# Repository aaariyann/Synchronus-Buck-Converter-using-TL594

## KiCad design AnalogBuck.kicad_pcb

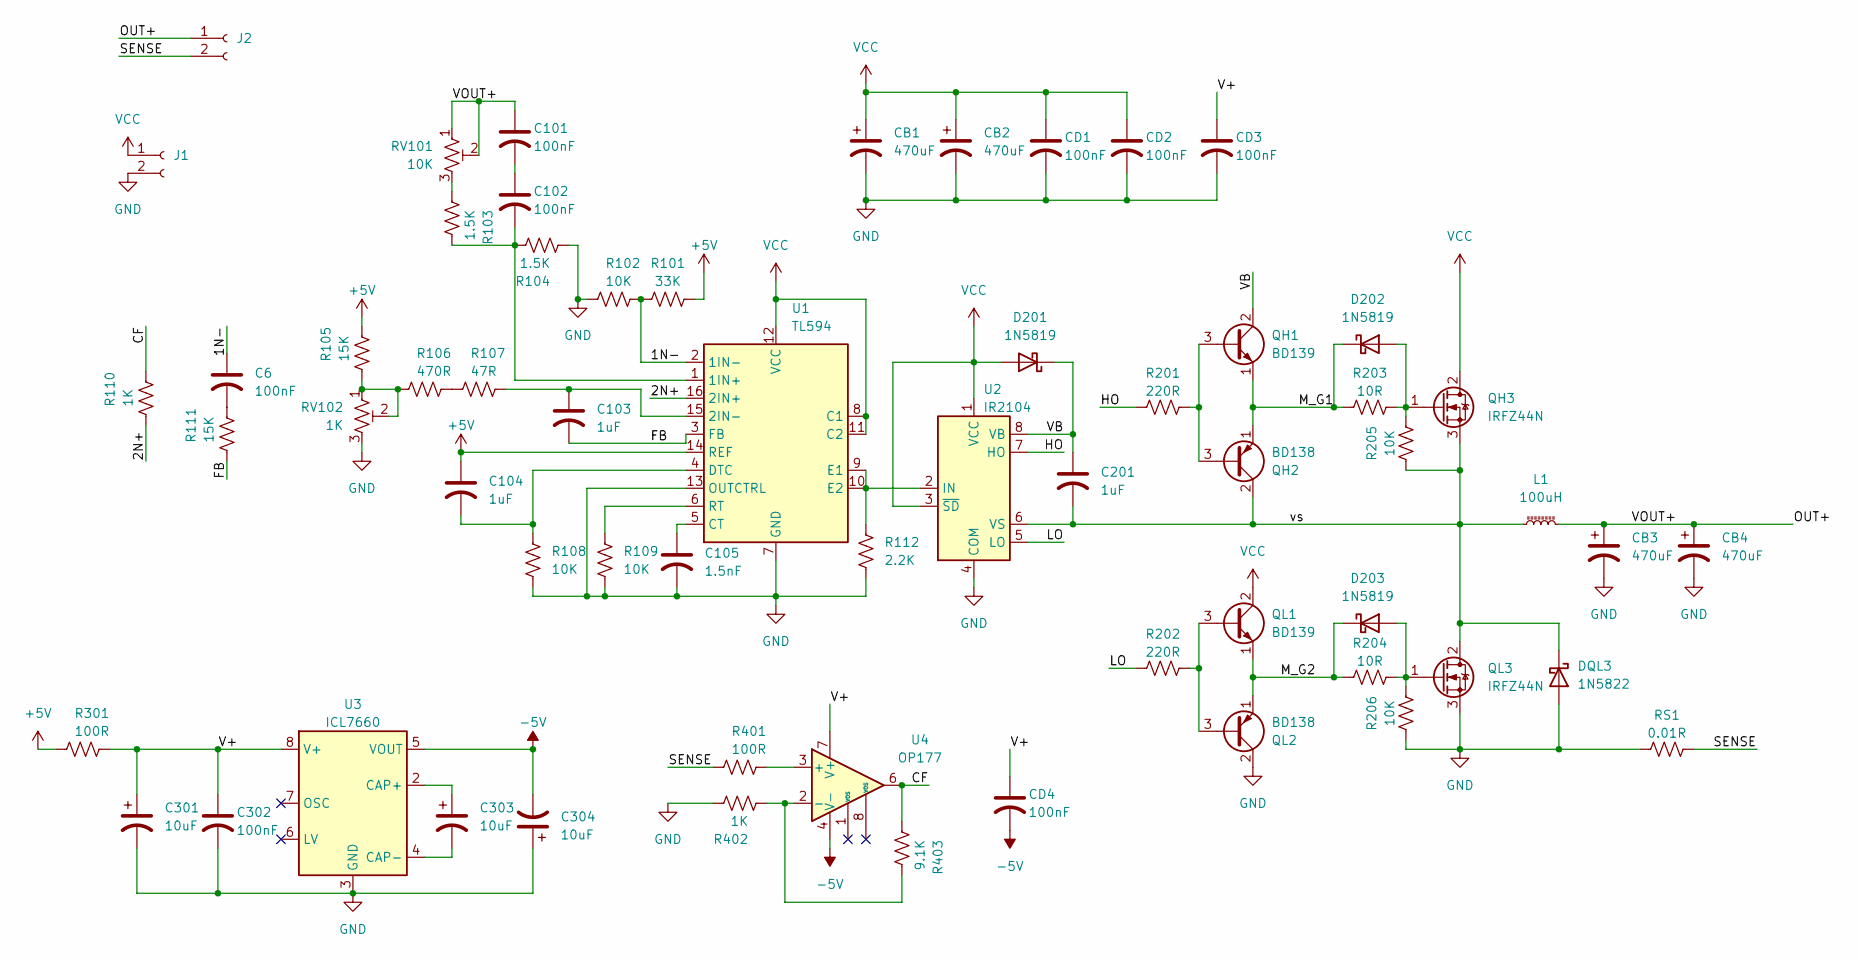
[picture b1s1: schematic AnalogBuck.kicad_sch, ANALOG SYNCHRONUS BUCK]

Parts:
C6, C101, C102, C302: 100nF; C_Disc_D5.0mm_W2.5mm_P5.00mm
C103, C104, C201: 1uF; C_Rect_L16.5mm_W4.7mm_P15.00mm_MKT
C105: 1.5nF; C_Rect_L7.0mm_W2.0mm_P5.00mm
C301, C303, C304: 10uF; CP_Radial_D5.0mm_P2.50mm
CB1, CB2, CB3, CB4: 470uF; CP_Radial_D8.0mm_P5.00mm
CD1, CD2, CD3, CD4: 100nF; C_Disc_D5.0mm_W2.5mm_P5.00mm
D201, D202, D203: 1N5819; D_DO-41_SOD81_P10.16mm_Horizontal
DQL3: 1N5822; D_DO-201AD_P15.24mm_Horizontal
J1, J2: Conn_01x02_Socket; TerminalBlock_Phoenix_MKDS-1,5-2_1x02_P5.00mm_Horizontal
L1: 100uH; L_Toroid_Vertical_L16.0mm_W8.0mm_P7.62mm
QH1: BD139; TO-126-3_Vertical
QH2: BD138; TO-126-3_Vertical
QH3: IRFZ44N; TO-220-3_Vertical
QL1: BD139; TO-126-3_Vertical
QL2: BD138; TO-126-3_Vertical
QL3: IRFZ44N; TO-220-3_Vertical
R101: 33K; R_Axial_DIN0207_L6.3mm_D2.5mm_P7.62mm_Horizontal
R102, R108, R109, R205, R206: 10K; R_Axial_DIN0207_L6.3mm_D2.5mm_P7.62mm_Horizontal
R103, R104: 1.5K; R_Axial_DIN0207_L6.3mm_D2.5mm_P7.62mm_Horizontal
R105, R111: 15K; R_Axial_DIN0207_L6.3mm_D2.5mm_P7.62mm_Horizontal
R106: 470R; R_Axial_DIN0207_L6.3mm_D2.5mm_P7.62mm_Horizontal
R107: 47R; R_Axial_DIN0207_L6.3mm_D2.5mm_P7.62mm_Horizontal
R110, R402: 1K; R_Axial_DIN0207_L6.3mm_D2.5mm_P7.62mm_Horizontal
R112: 2.2K; R_Axial_DIN0207_L6.3mm_D2.5mm_P7.62mm_Horizontal
R201, R202: 220R; R_Axial_DIN0207_L6.3mm_D2.5mm_P7.62mm_Horizontal
R203, R204: 10R; R_Axial_DIN0207_L6.3mm_D2.5mm_P7.62mm_Horizontal
R301, R401: 100R; R_Axial_DIN0207_L6.3mm_D2.5mm_P7.62mm_Horizontal
R403: 9.1K; R_Axial_DIN0207_L6.3mm_D2.5mm_P7.62mm_Horizontal
RS1: 0.01R; R_2512_6332Metric_Pad1.40x3.35mm_HandSolder
RV101: 10K; Potentiometer_Bourns_3296W_Vertical
RV102: 1K; Potentiometer_Bourns_3296W_Vertical
U1: TL594; DIP-16_W10.16mm_LongPads
U2: IR2104; DIP-8_W7.62mm_LongPads
U3: ICL7660; DIP-8_W7.62mm_LongPads
U4: OP177; DIP-8_W7.62mm_LongPads

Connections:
+5V: C104.1, R101.2, R105.1, R301.2, U1.14 (REF)
-5V: C304.2, CD4.2, U3.5 (VOUT), U4.4 (V-)
/1N-: C6.1, R101.1, R102.1, U1.2 (1IN-)
/2N+: R110.2, U1.16 (2IN+)
/CF: R110.1, R403.2, U4.6
/FB: C103.2, R111.2, U1.3 (FB)
/HO: R201.2, U2.7 (HO)
/LO: R202.2, U2.5 (LO)
/M_G1: D202.1 (K), QH1.1 (E), QH2.1 (E), R203.2
/M_G2: D203.1 (K), QL1.1 (E), QL2.1 (E), R204.2
/OUT+: C101.1, CB3.1, CB4.1, J2.1, L1.2, RV101.1, RV101.2
/SENSE: J2.2, R401.2, RS1.1
/V+: C301.1, C302.1, CD3.1, CD4.1, R301.1, U3.8 (V+), U4.7 (V+)
/VB: C201.1, D201.1 (K), QH1.2 (C), U2.8 (VB)
/vs: C201.2, DQL3.1 (K), L1.1, QH2.2 (C), QH3.3 (S), QL3.2 (D), R205.2, U2.6 (VS)
GND: C105.2, C301.2, C302.2, C304.1, CB1.2, CB2.2, CB3.2, CB4.2, CD1.2, CD2.2, CD3.2, DQL3.2 (A), J1.2, QL2.2 (C), QL3.3 (S), R102.2, R104.2, R108.2, R109.2, R112.2, R206.2, R402.1, RS1.2, RV102.3, U1.7 (GND), U1.13 (OUTCTRL), U2.4 (COM), U3.3 (GND)
unnamed: C6.2, R111.1
unnamed: C101.2, C102.1
unnamed: D202.2 (A), QH3.1 (G), R203.1, R205.1
unnamed: D203.2 (A), QL3.1 (G), R204.1, R206.1
unnamed: QH1.3 (B), QH2.3 (B), R201.1
unnamed: QL1.3 (B), QL2.3 (B), R202.1
unnamed: R103.2, RV101.3
unnamed: R105.2, R106.2, RV102.1, RV102.2
unnamed: R106.1, R107.2
unnamed: C102.2, R103.1, R104.1, U1.1 (1IN+)
unnamed: C103.1, R107.1, U1.15 (2IN-)
unnamed: C105.1, U1.5 (CT)
unnamed: C104.2, R108.1, U1.4 (DTC)
unnamed: R112.1, U1.9 (E1), U1.10 (E2), U2.2 (IN)
unnamed: R109.1, U1.6 (RT)
unnamed: C303.1, U3.2 (CAP+)
unnamed: C303.2, U3.4 (CAP-)
unnamed: R401.1, U4.3 (+)
unnamed: R402.2, R403.1, U4.2 (-)
VCC: CB1.1, CB2.1, CD1.1, CD2.1, D201.2 (A), J1.1, QH3.2 (D), QL1.2 (C), U1.8 (C1), U1.11 (C2), U1.12 (VCC), U2.1 (VCC), U2.3 (~SD)

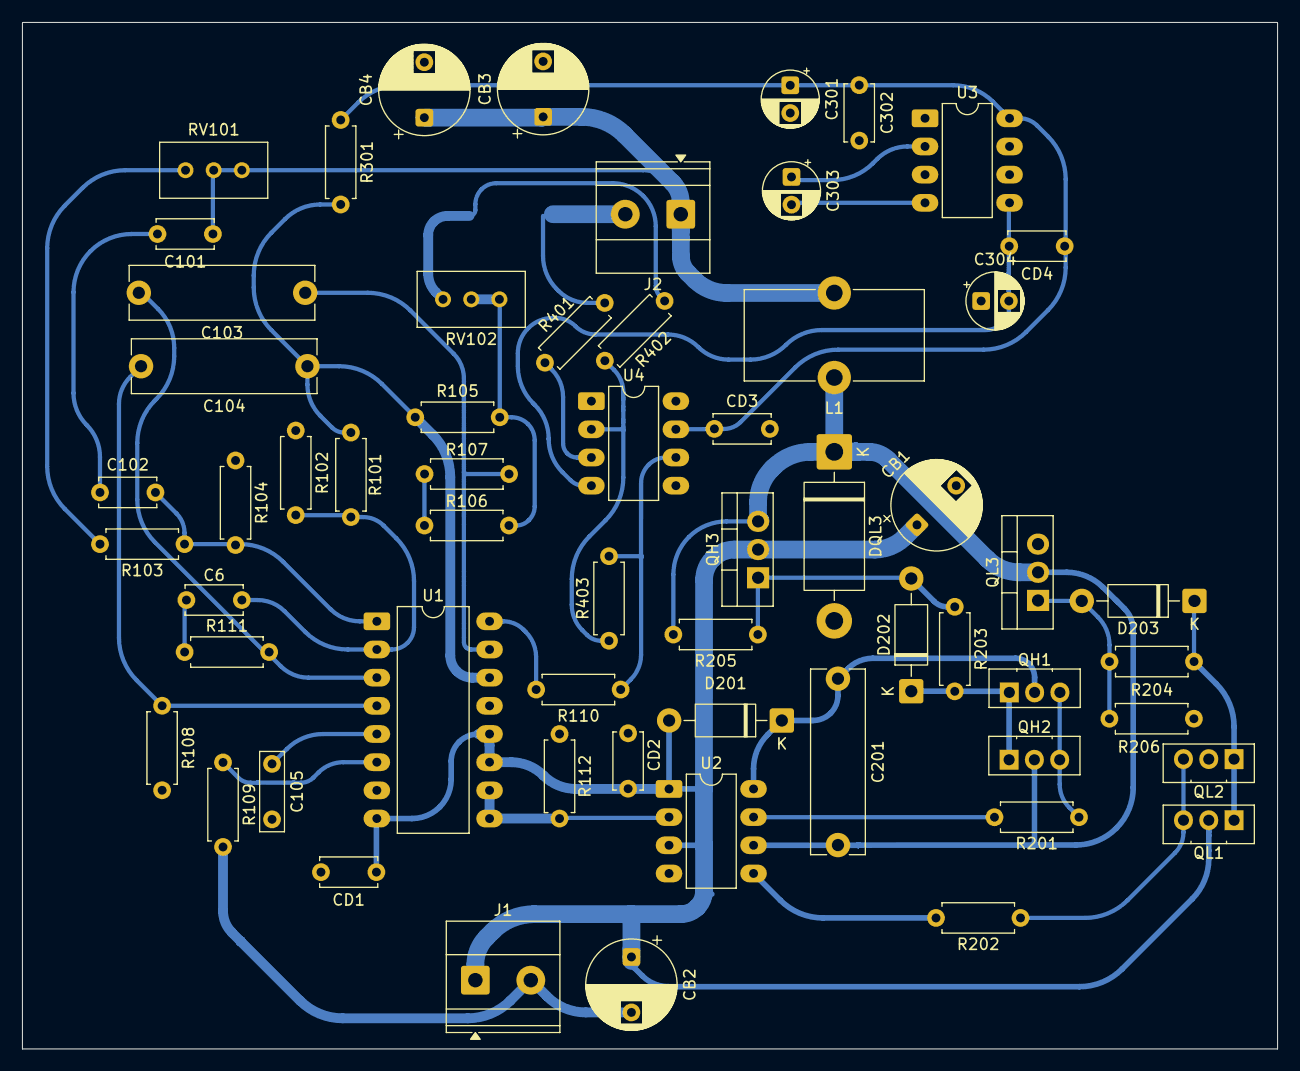
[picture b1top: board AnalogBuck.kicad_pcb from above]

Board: 2 copper layers, 113.2 x 92.5 mm, 61 parts (1 on the bottom side), 36 nets.
